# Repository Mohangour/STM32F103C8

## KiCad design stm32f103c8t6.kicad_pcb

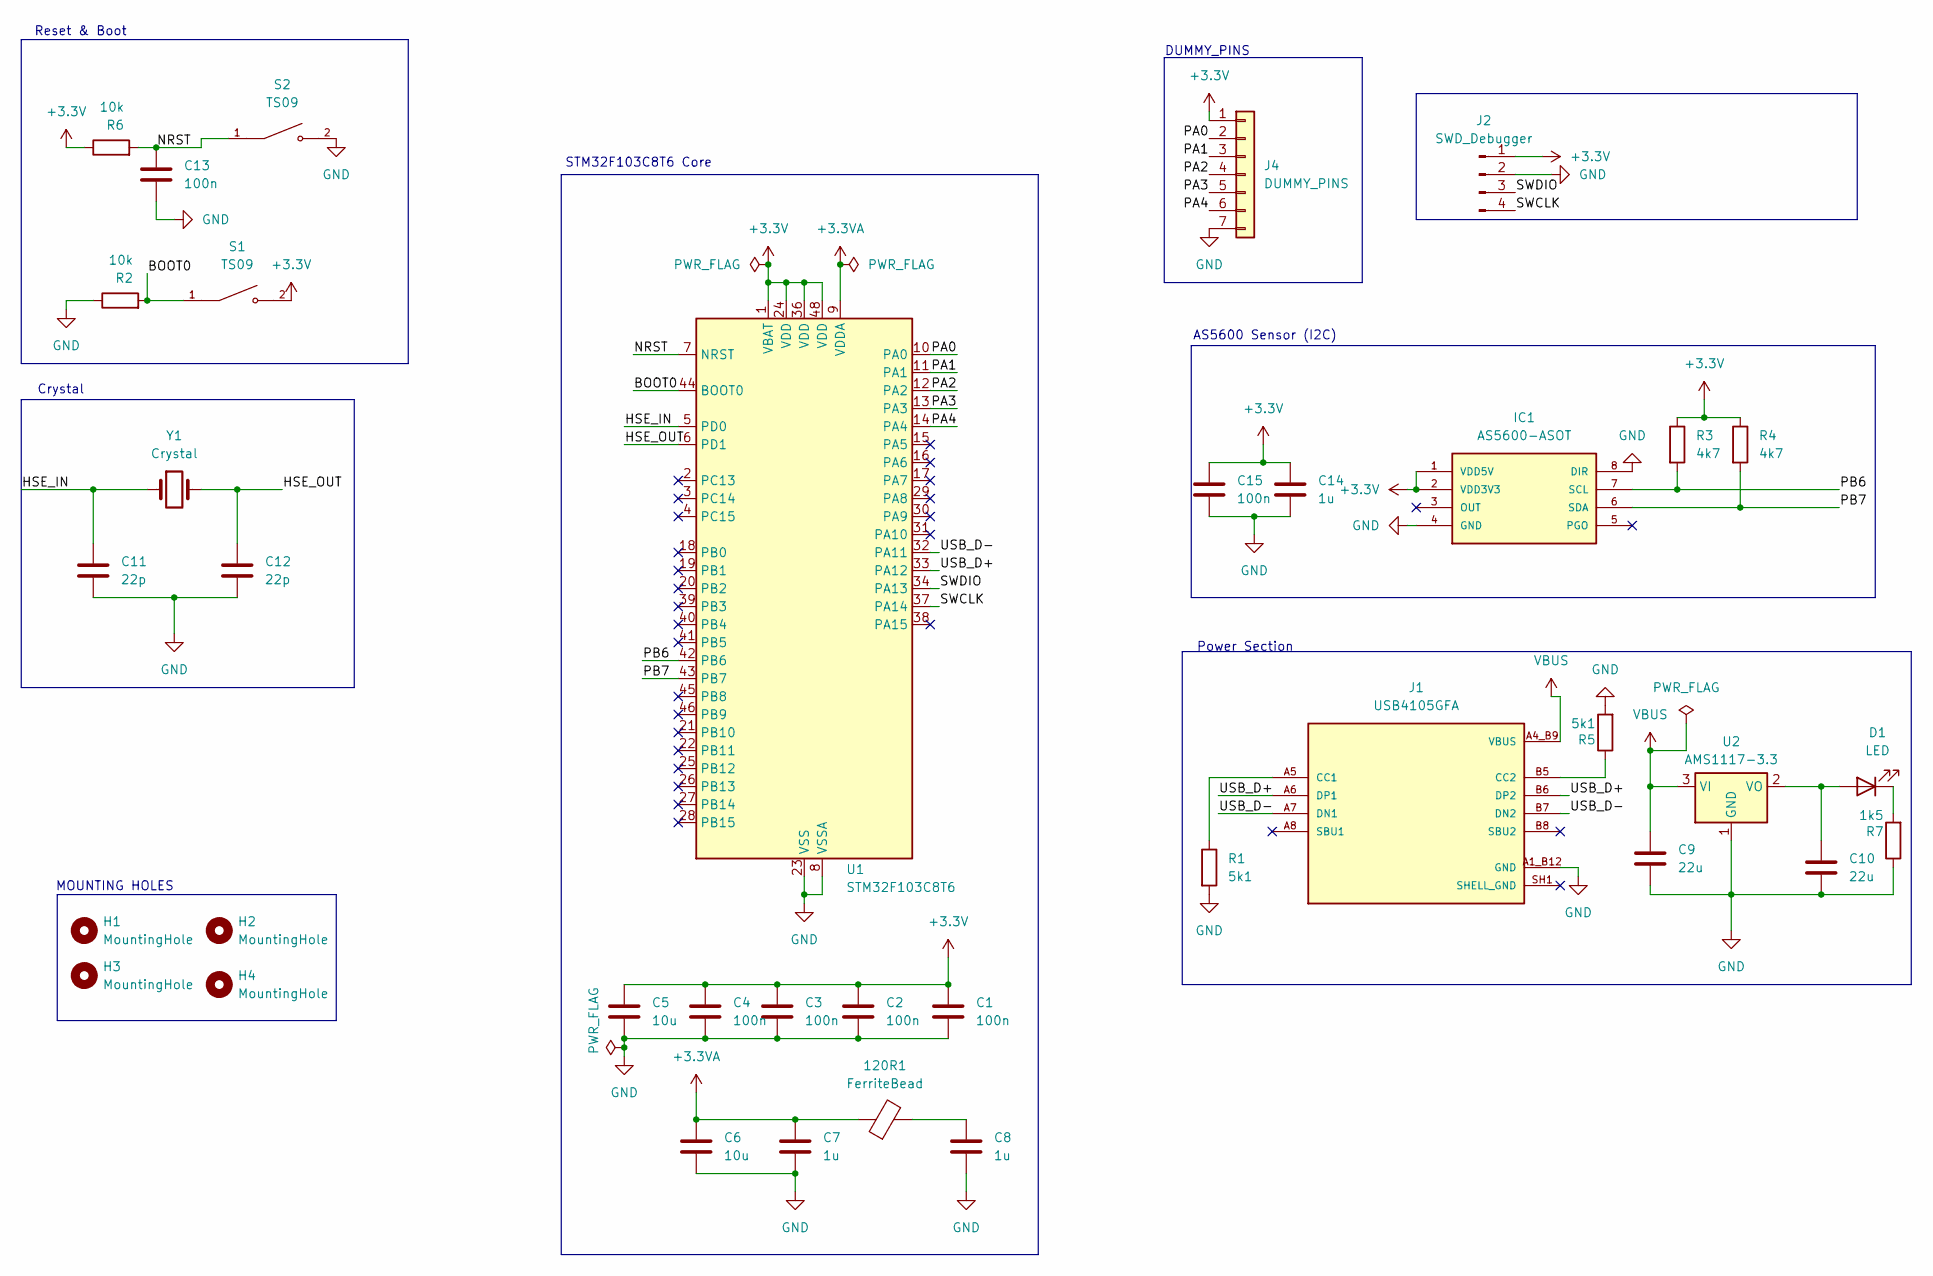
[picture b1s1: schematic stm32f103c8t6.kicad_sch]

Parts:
120R1: FerriteBead; BEADC0603X33N
C1, C2, C3, C4, C13, C15: 100n; C_0603_1608Metric
C5, C6: 10u; C_0603_1608Metric
C7, C8, C14: 1u; C_0603_1608Metric
C9, C10: 22u; C_0603_1608Metric
C11, C12: 22p; C_0603_1608Metric
D1: LED; LED_0603_1608Metric
H1, H2, H3, H4: MountingHole; MountingHole_2.1mm
IC1: AS5600-ASOT; SOIC127P600X175-8N; MOUSER_PART_NUMBER 985-AS5600-ASOT
J1: USB4105GFA; GCT_USB4105GFA; PARTREV B3
J2: SWD_Debugger; PinHeader_1x04_P2.54mm_Vertical
J4: DUMMY_PINS; PinHeader_1x07_P2.54mm_Vertical
R1, R5: 5k1; R_0603_1608Metric
R2, R6: 10k; R_0603_1608Metric
R3, R4: 4k7; R_0603_1608Metric
R7: 1k5; R_0603_1608Metric
S1, S2: TS09; SW_TS09-63-25-R-160-SMT-TR; PARTREV 1.0
U1: STM32F103C8T6; LQFP-48_7x7mm_P0.5mm
U2: AMS1117-3.3; SOT-223-3_TabPin2
Y1: Crystal; Crystal_SMD_0603-2Pin_6.0x3.5mm

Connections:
+3.3V: C1.1, C2.1, C3.1, C4.1, C5.1, C14.1, C15.1, IC1.1 (VDD5V), IC1.2 (VDD3V3), J2.1, J4.1, R3.1, R4.1, R6.1, S1.2, U1.1 (VBAT), U1.24 (VDD), U1.36 (VDD), U1.48 (VDD)
+3.3VA: 120R1.1, C6.1, C7.1, U1.9 (VDDA)
/BOOT0: R2.2, S1.1, U1.44 (BOOT0)
/HSE_IN: C11.1, U1.5 (PD0), Y1.1
/HSE_OUT: C12.1, U1.6 (PD1), Y1.2
/NRST: C13.1, R6.2, S2.1, U1.7 (NRST)
/PA0: J4.2, U1.10 (PA0)
/PA1: J4.3, U1.11 (PA1)
/PA2: J4.4, U1.12 (PA2)
/PA3: J4.5, U1.13 (PA3)
/PA4: J4.6, U1.14 (PA4)
/PB6: IC1.7 (SCL), R3.2, U1.42 (PB6)
/PB7: IC1.6 (SDA), R4.2, U1.43 (PB7)
/SWCLK: J2.4, U1.37 (PA14)
/SWDIO: J2.3, U1.34 (PA13)
/USB_D+: J1.A6 (DP1), J1.B6 (DP2), U1.33 (PA12)
/USB_D-: J1.A7 (DN1), J1.B7 (DN2), U1.32 (PA11)
GND: C1.2, C2.2, C3.2, C4.2, C5.2, C6.2, C7.2, C8.2, C9.2, C10.2, C11.2, C12.2, C13.2, C14.2, C15.2, IC1.4 (GND), IC1.8 (DIR), J1.A1_B12 (GND), J1.B1_A12 (GND), J2.2, J4.7, R1.2, R2.1, R5.2, R7.1, S2.2, U1.8 (VSSA), U1.23 (VSS), U1.35 (VSS), U1.47 (VSS), U2.1 (GND)
unnamed: 120R1.2, C8.1
unnamed: C10.1, D1.2 (A), U2.2 (VO)
unnamed: D1.1 (K), R7.2
unnamed: J1.A5 (CC1), R1.1
unnamed: J1.B5 (CC2), R5.1
VBUS: C9.1, J1.A4_B9 (VBUS), J1.B4_A9 (VBUS), U2.3 (VI)

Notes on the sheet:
MOUNTING HOLES
AS5600 Sensor (I2C)
STM32F103C8T6 Core
Reset & Boot
DUMMY_PINS
Power Section
Crystal

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
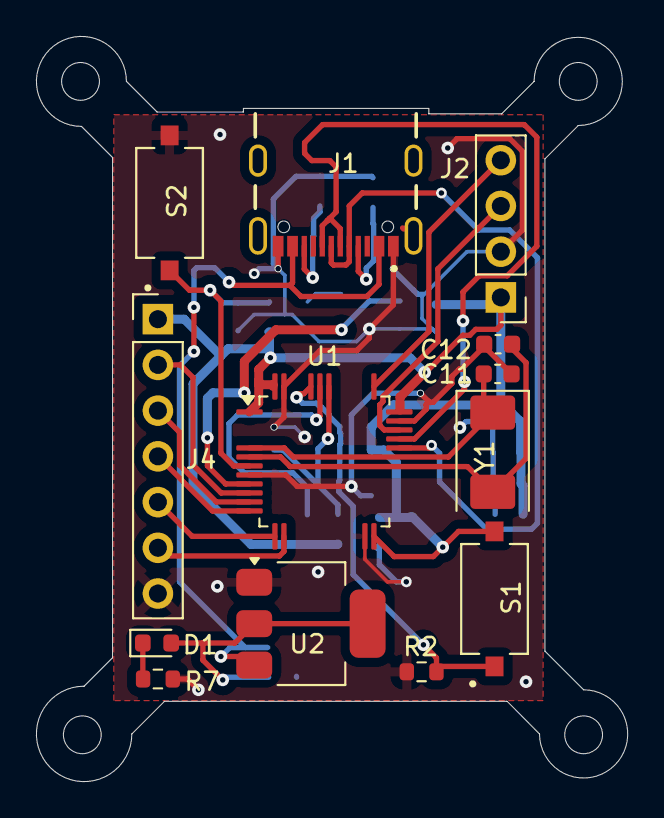
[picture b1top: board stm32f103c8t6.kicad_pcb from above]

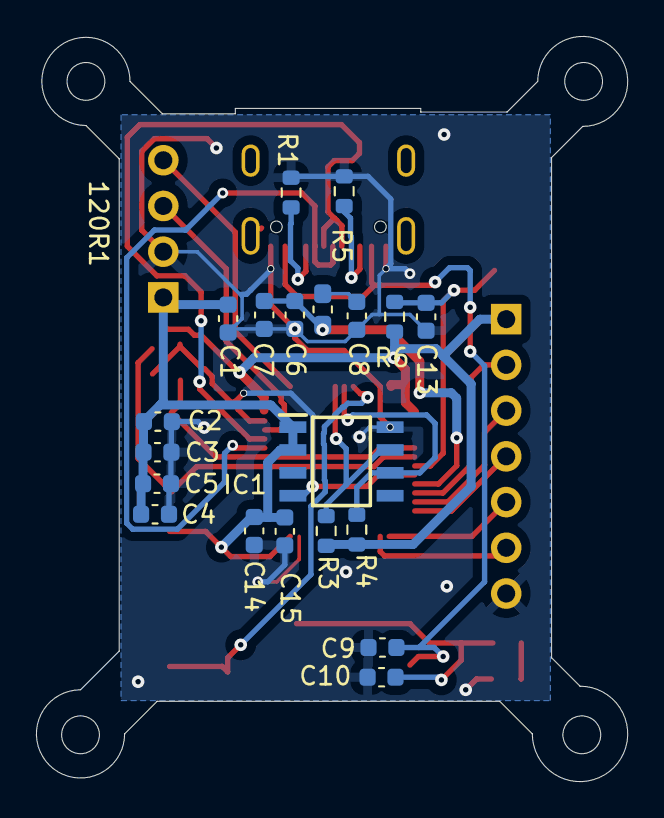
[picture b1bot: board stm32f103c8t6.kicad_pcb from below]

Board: 2 copper layers, 32.8 x 41.4 mm, 37 parts (20 on the bottom side), 24 nets.

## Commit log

2026-02-18 Add files via upload
    before changing the traces
2026-02-19 Add files via upload
    final pcb before mounting holes
2026-02-20 Add files via upload
    final pcb with mounting holes before DFM check
2026-02-20 Add files via upload
    after DFM check
